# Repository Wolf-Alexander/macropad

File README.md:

# my_macropad

A custom 3x3 mechanical macropad based on the Seed Studio XIAO RP2040.

## Features

- 9-key mechanical macro pad
- XIAO RP2040 microcontrollre
- KMK firmware (CircuitPython)
- USB-C connectivity
- Custom PCB designed in KiCad
- Custom 3D-printed enclosure
- MX-compatible switches

## Design

## Schematic

## PCB layout

## Case

## Bill of Materials

| Component | Quantity | Notes |
|-----------|----------|-------|
| Seeed Studio XIAO RP2040 | 1 | Main microcontroller |
| MX Switches | 9 | Mechanical keyboard switches |
| Keycaps | 9 | MX-compatible |
| 1N3138 Diodes | 9 | One per switch |
| Custom PCB | 1 | Designed in KiCad |
| Top Plate | 1 | 3D printed |
| Bottom Case | 1 | 3D printed |
| M3 Heatset Inserts (5x4 mm) | 4 | Threaded inserts |
| M3 Screws | 4 | Case assembly |
| USB-C Cable | 1 | For power and data |

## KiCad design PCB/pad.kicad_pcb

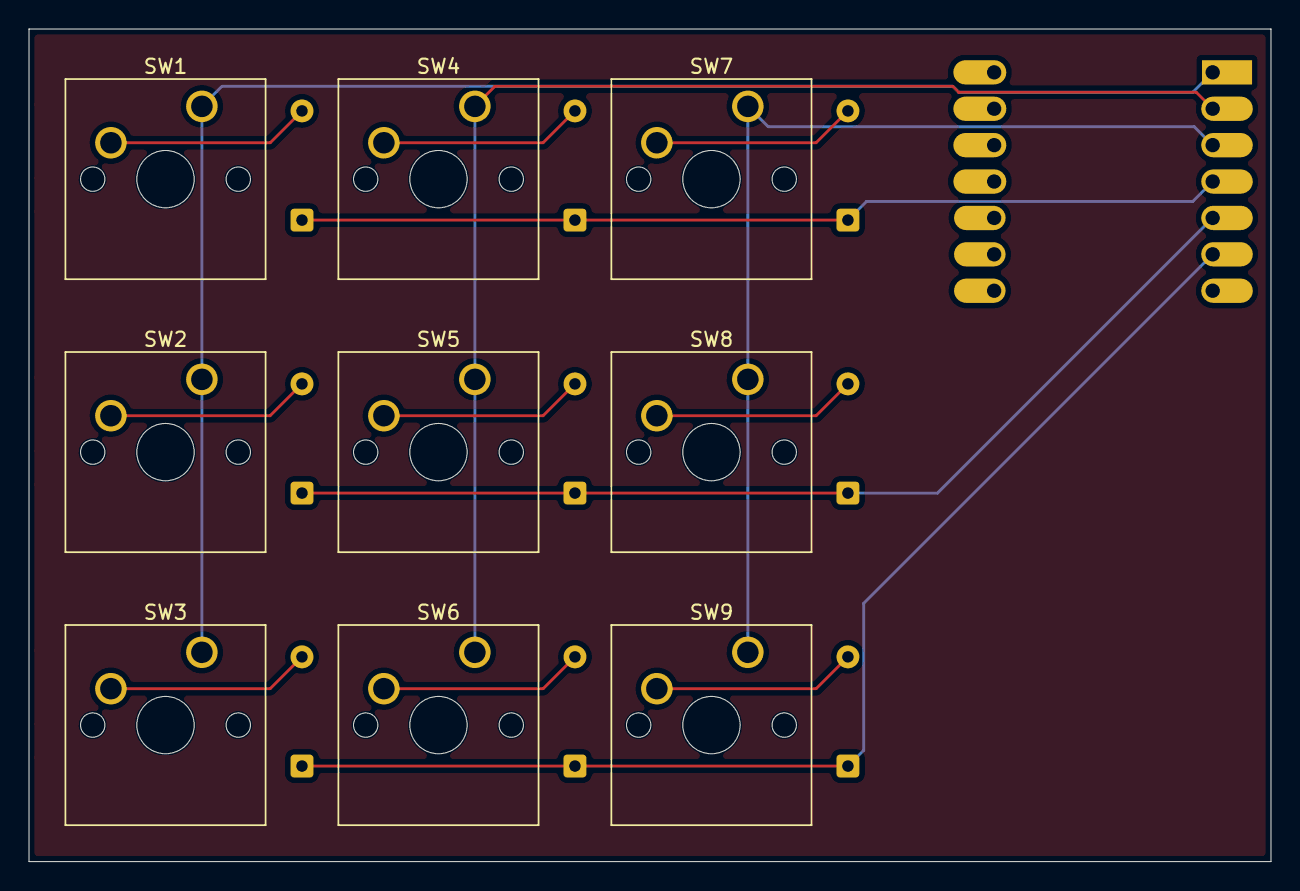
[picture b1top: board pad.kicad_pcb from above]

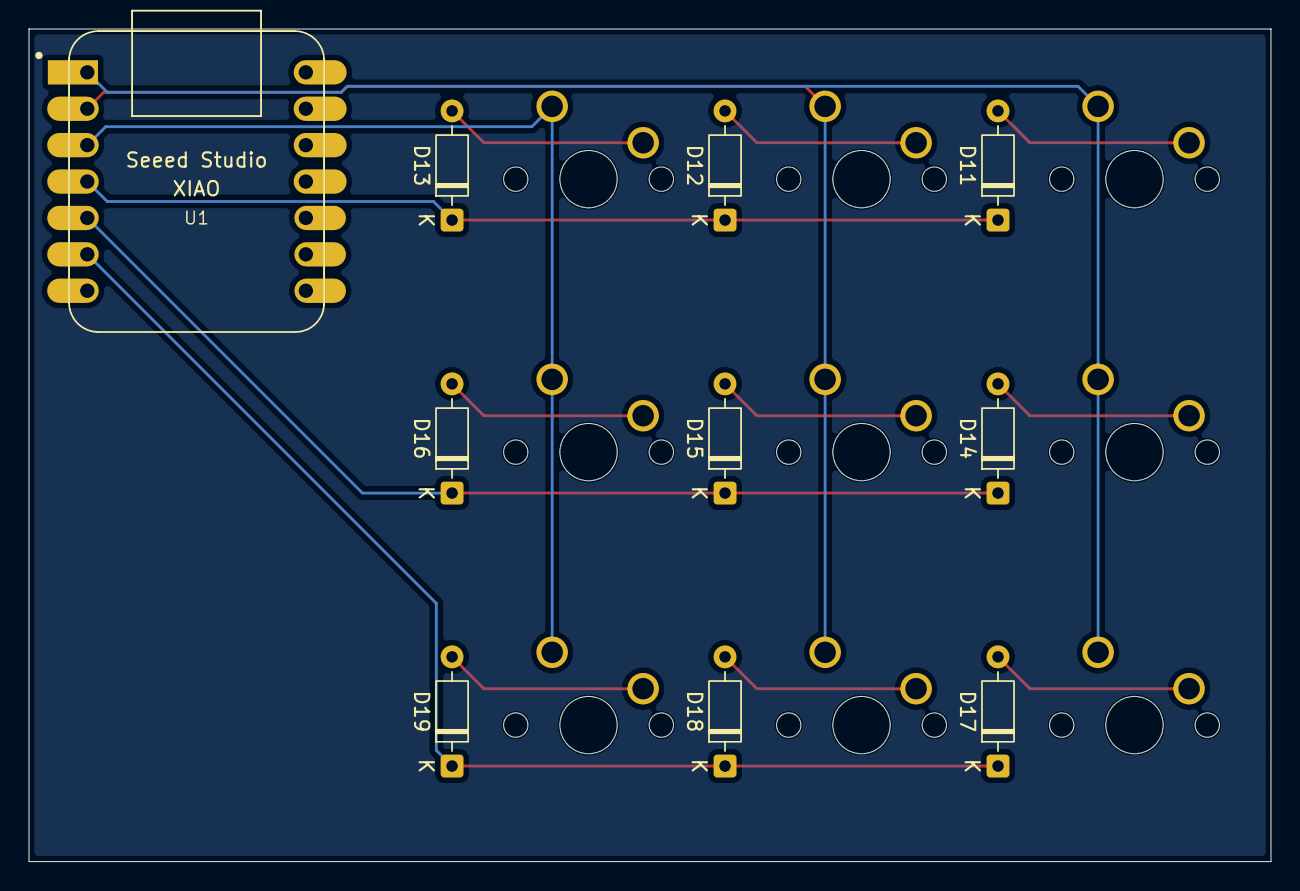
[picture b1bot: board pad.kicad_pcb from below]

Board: 2 copper layers, 86.7 x 58.1 mm, 19 parts (10 on the bottom side), 15 nets.

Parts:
D11, D12, D13, D14, D15, D16, D17, D18, D19: 1N4148; D_DO-35_SOD27_P7.62mm_Horizontal
SW1, SW2, SW3, SW4, SW5, SW6, SW7, SW8, SW9: SW_Push; SW_Cherry_MX_1.00u_PCB
U1: MOUDLE-SEEEDUINO-XIAO; XIAO-Generic-Hybrid-14P-2.54-21X17.8MM

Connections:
/Col0: SW1.1, SW2.1, SW3.1, U1.1 (PA02_A0_D0)
/Col1: SW4.1, SW5.1, SW6.1, U1.2 (PA4_A1_D1)
/Col2: SW7.1, SW8.1, SW9.1, U1.3 (PA10_A2_D2)
/Row0: D11.1 (K), D12.1 (K), D13.1 (K), U1.4 (PA11_A3_D3)
/Row1: D14.1 (K), D15.1 (K), D16.1 (K), U1.5 (PA8_A4_D4_SDA)
/Row2: D17.1 (K), D18.1 (K), D19.1 (K), U1.6 (PA9_A5_D5_SCL)
unnamed: D11.2 (A), SW1.2
unnamed: D12.2 (A), SW4.2
unnamed: D13.2 (A), SW7.2
unnamed: D14.2 (A), SW2.2
unnamed: D15.2 (A), SW5.2
unnamed: D16.2 (A), SW8.2
unnamed: D17.2 (A), SW3.2
unnamed: D18.2 (A), SW6.2
unnamed: D19.2 (A), SW9.2
